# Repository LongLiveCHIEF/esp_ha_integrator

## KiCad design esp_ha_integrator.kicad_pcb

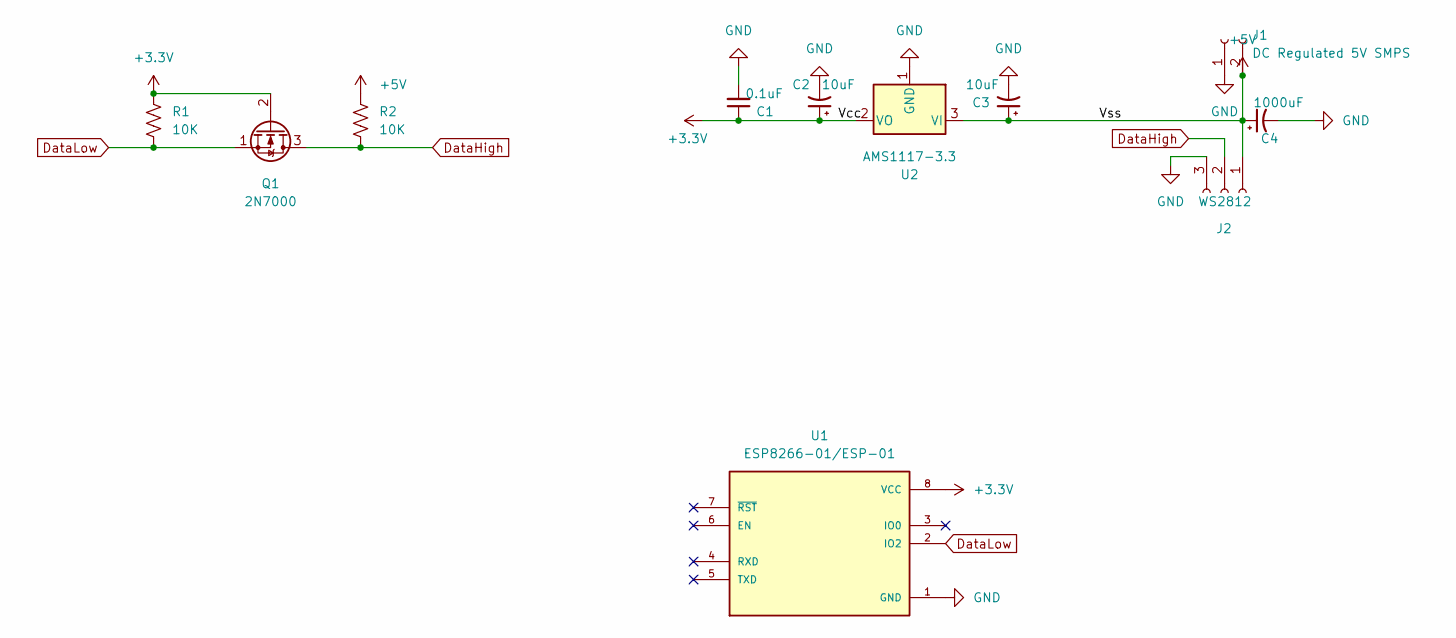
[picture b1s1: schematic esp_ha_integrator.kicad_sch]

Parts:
C1: 0.1uF; C_Disc_D5.0mm_W2.5mm_P2.50mm
C2, C3: 10uF; CP_Radial_D4.0mm_P2.00mm
C4: 1000uF; CP_Radial_D10.0mm_P3.80mm
J1: DC Regulated 5V SMPS; JST_XH_initeq_1_02_p2_50
J2: WS2812; JST_XH_S3B-XH-A_1x03_P2.50mm_Horizontal
Q1: 2N7000; TO-92_Inline
R1, R2: 10K; R_Axial_DIN0207_L6.3mm_D2.5mm_P10.16mm_Horizontal
U1: ESP8266-01/ESP-01; XCVR_ESP8266-01/ESP-01; PARTREV V1.2
U2: AMS1117-3.3; SOT-223-3_TabPin2

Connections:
+3V3: C1.1, C2.1, Q1.2 (G), R1.1, U1.8 (VCC), U2.2 (VO)
+5V: C3.1, C4.1, J1.2, J2.1, R2.1, U2.3 (VI)
DataHigh: J2.2, Q1.3 (D), R2.2
DataLow: Q1.1 (S), R1.2, U1.2 (IO2)
GND: C1.2, C2.2, C3.2, C4.2, J1.1, J2.3, U1.1 (GND), U2.1 (GND)

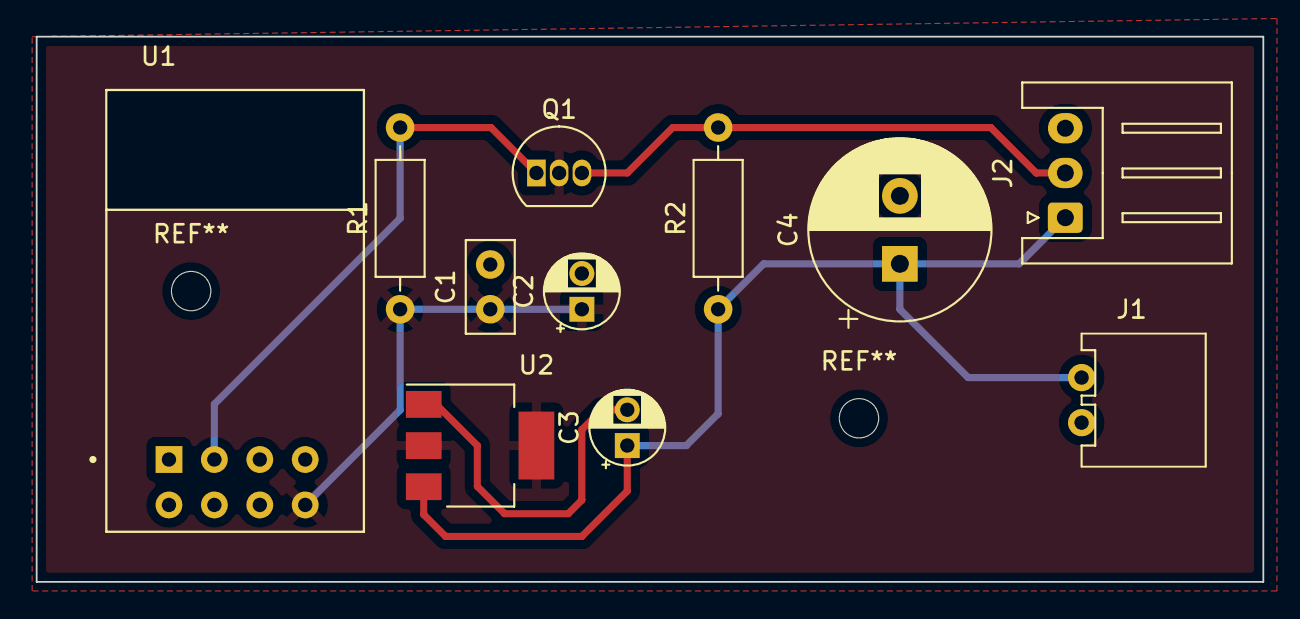
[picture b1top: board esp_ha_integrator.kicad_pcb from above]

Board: 2 copper layers, 68.6 x 30.5 mm, 11 parts (0 on the bottom side), 5 nets.

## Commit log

2022-07-17 gerbers
2022-07-17 remove zip
2022-07-22 updated board and created mill_drill folder
2022-07-22 remove backups
2022-07-22 add license
2022-07-22 remove flatcam.Flatprj
    the real flatcam project is in the mill_drills folder
2022-07-22 add copper fill on top
2022-07-22 update 3v3 net traces
2022-07-22 trace tweaks
2022-07-22 add README.md
2022-07-22 started creating geometry and jobs for cnc
2022-07-22 resetting all geometry
2022-07-22 rotate u2 and c3
